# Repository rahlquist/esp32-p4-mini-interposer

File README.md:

# ESP32-P4-Mini Interposer

A small break-out / **interposer** board for the **Spotpear (Waveshare-style) ESP32-P4-Mini development
board** (`ESP32P4-MINI-A`) that adapts its fine-pitch headers up to breadboard-friendly spacing.

## What the board is for

The ESP32-P4-Mini exposes its GPIO on **three dual-row 1.27 mm pin headers** — one on the **left edge (P1)**,
one on the **right edge (P2)**, and one along the **bottom edge (P3)**. 1.27 mm headers are too narrow and
fragile to plug directly into a standard solderless breadboard, which uses 2.54 mm spacing.

This interposer carries **three 1.27 mm female sockets laid out exactly where the Mini's headers are**, so
the Mini plugs down onto it level, and re-routes every one of the 104 pins to **three 2.54 mm single-row
male headers** for easy breadboard / jumper use.

```
       ┌────────────────────────────────────────────┐
       │   P1 (left, vertical)   ──►  J4 (2.54 mm)  │
  Mini │   P2 (right, vertical)  ──►  J5 (2.54 mm)  │
       │   P3 (bottom, horizontal)──► J6 (2.54 mm)  │
       └────────────────────────────────────────────┘
```

The board is a pure passive **1:1 passthrough** — each 1.27 mm input pin is routed straight to the
corresponding 2.54 mm output pin (no level shifting, no logic).

## Key facts

| | |
|---|---|
| Origin board | Spotpear `ESP32P4-MINI-A` — 23.4 × 31.25 mm, ESP32-P4 + ESP32-C6 |
| Input headers | P1 (left, 2×17), P2 (right, 2×17), P3 (bottom, 2×18) — all **1.27 mm** |
| Output headers | J4 (1×34), J5 (1×34), J6 (1×36) — all **2.54 mm** single-row |
| Total nets | 104, one per pin |
| Routing | 2-layer, Freerouting auto-routed; DRC clean (0 unconnected / 0 violations) |
| Silkscreen | Each 2.54 mm output pin labelled with its GPIO / signal name |
| Design | KiCad 10.0.6 (schematic + board) |

## Repository layout

```
.
├── kicad/                 KiCad design source and exports
│   ├── p4-mini-interposer.kicad_sch     schematic
│   ├── p4-mini-interposer.kicad_pcb     routed board
│   ├── p4-mini-interposer.kicad_pro     project
│   ├── p4-mini-interposer.pdf           schematic PDF
│   ├── p4-mini-interposer-routed.pdf    routed board PDF
│   ├── p4-mini-interposer-green.pdf     board render (green solder mask)
│   ├── p4-mini-interposer.ses           Freerouting session
│   └── p4-mini-interposer-bom.csv       bill of materials
├── reference/            Documents/source material the original board is built from
│   ├── esp32p4-mini.pdf   (Spotpear board schematic)
│   ├── esp32-p4-ext.pdf   (extension board schematic)
│   ├── esp32p4-mini.step / esp32p4-mini-2.step   (3D models)
│   └── *.jpg              (board photos)
└── docs/board-preview.png
```

> The files under `reference/` are the source documentation for the **Spotpear ESP32-P4-Mini** board and
> are the property of their respective authors (Spotpear / Waveshare); they are included for reference and
> are not covered by this project's license. The `kicad/` files are this interposer's own design.

## Silkscreen pinout

Each 2.54 mm output header pin is labelled with the function it connects to. Net mapping is a plain 1:1
passthrough, so output header **J4 pin N ↔ mini P1 pin N** (and likewise J5↔P2, J6↔P3):

| Output | Source header | Signals (by pin) |
|---|---|---|
| **J4** | **P1** (left, vertical) | D−, D+, GPIO31…53, 5V, 1V8, 3V3, GND |
| **J5** | **P2** (right, vertical) | GPIO0…30, SDA, SCL, RESET, 5V, 3V3, GND |
| **J6** | **P3** (bottom, horizontal) | I2C0_SDA/SCL, GPIO6/14–19/54, DSI±/CSI±, USBD±, 3V3, GND |

## Status

- Schematic **ERC clean** and board **DRC clean** (104/104 nets routed, 0 violations).
- Header positions on the interposer were derived from the Mini's 23.4 × 31.25 mm form factor and measured
  header spans (P1–P2 outer span 22.2 mm, P1 vertical span 20.7 mm, P3 span 21.9 mm, P3 set 1 mm off the
  bottom edge). **A physical fit-test against the actual board is recommended before fabrication.**

## License

This interposer design (the `kicad/` files and this README) is licensed under the MIT License — see
[LICENSE](LICENSE). Reference/vendor documents in `reference/` remain the property of their authors.

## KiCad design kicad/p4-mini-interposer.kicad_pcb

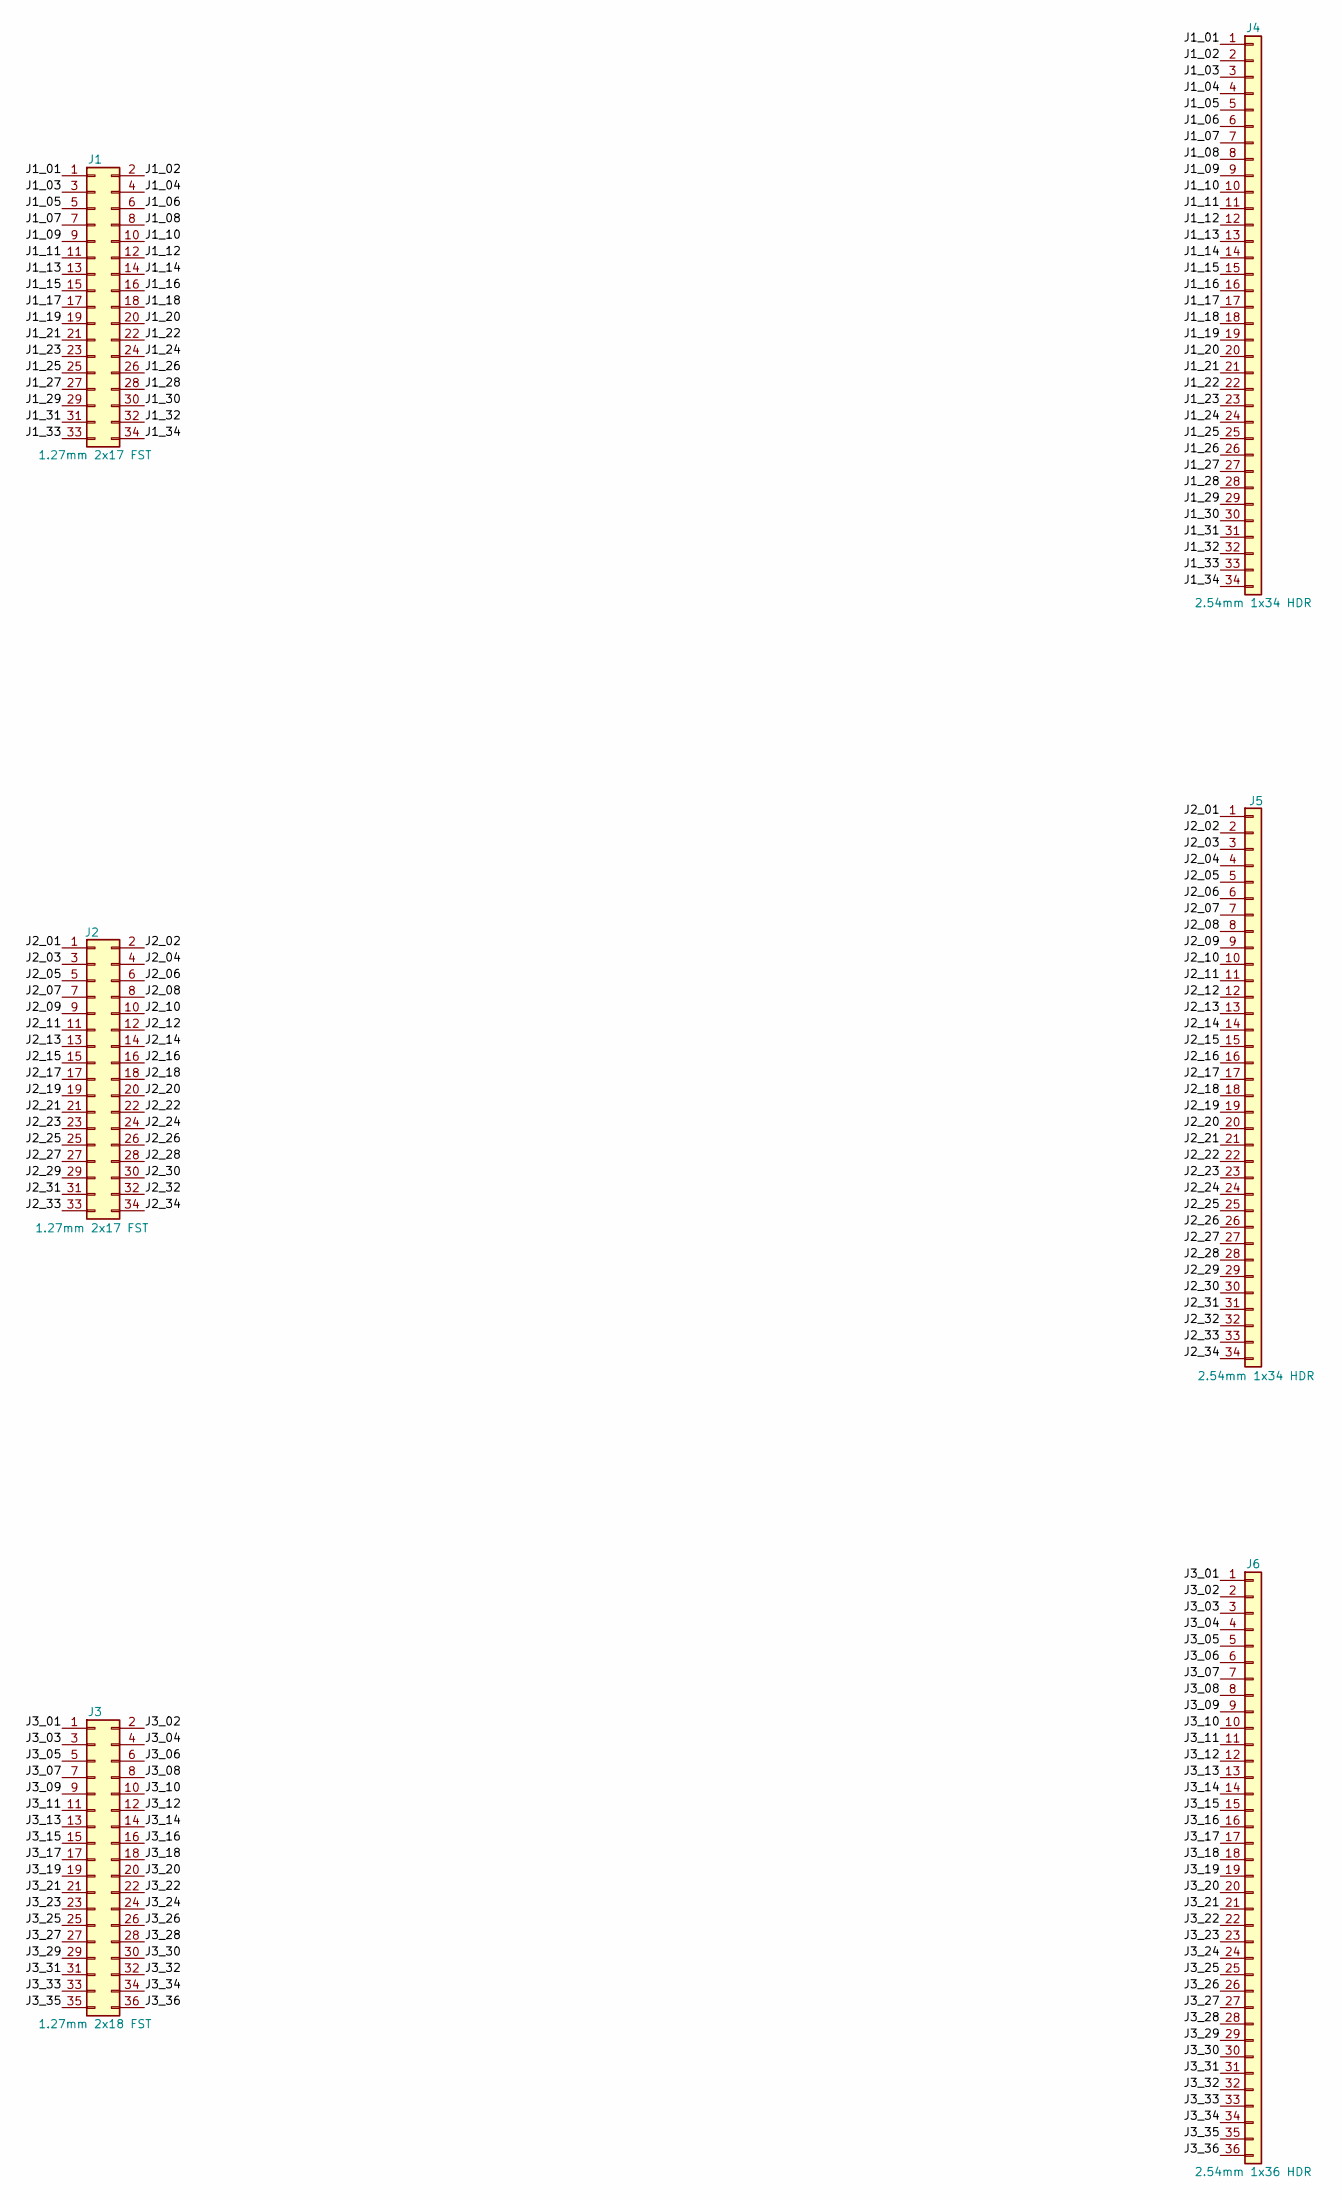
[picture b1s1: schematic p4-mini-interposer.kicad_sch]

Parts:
J1, J2: 1.27mm 2x17 FST; PinHeader_2x17_P1.27mm_Vertical
J3: 1.27mm 2x18 FST; PinHeader_2x18_P1.27mm_Vertical
J4, J5: 2.54mm 1x34 HDR; PinHeader_1x34_P2.54mm_Vertical
J6: 2.54mm 1x36 HDR; PinHeader_1x36_P2.54mm_Vertical

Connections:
/J1_01: J1.1, J4.1
/J1_02: J1.2, J4.2
/J1_03: J1.3, J4.3
/J1_04: J1.4, J4.4
/J1_05: J1.5, J4.5
/J1_06: J1.6, J4.6
/J1_07: J1.7, J4.7
/J1_08: J1.8, J4.8
/J1_09: J1.9, J4.9
/J1_10: J1.10, J4.10
/J1_11: J1.11, J4.11
/J1_12: J1.12, J4.12
/J1_13: J1.13, J4.13
/J1_14: J1.14, J4.14
/J1_15: J1.15, J4.15
/J1_16: J1.16, J4.16
/J1_17: J1.17, J4.17
/J1_18: J1.18, J4.18
/J1_19: J1.19, J4.19
/J1_20: J1.20, J4.20
/J1_21: J1.21, J4.21
/J1_22: J1.22, J4.22
/J1_23: J1.23, J4.23
/J1_24: J1.24, J4.24
/J1_25: J1.25, J4.25
/J1_26: J1.26, J4.26
/J1_27: J1.27, J4.27
/J1_28: J1.28, J4.28
/J1_29: J1.29, J4.29
/J1_30: J1.30, J4.30
/J1_31: J1.31, J4.31
/J1_32: J1.32, J4.32
/J1_33: J1.33, J4.33
/J1_34: J1.34, J4.34
/J2_01: J2.1, J5.1
/J2_02: J2.2, J5.2
/J2_03: J2.3, J5.3
/J2_04: J2.4, J5.4
/J2_05: J2.5, J5.5
/J2_06: J2.6, J5.6
/J2_07: J2.7, J5.7
/J2_08: J2.8, J5.8
/J2_09: J2.9, J5.9
/J2_10: J2.10, J5.10
/J2_11: J2.11, J5.11
/J2_12: J2.12, J5.12
/J2_13: J2.13, J5.13
/J2_14: J2.14, J5.14
/J2_15: J2.15, J5.15
/J2_16: J2.16, J5.16
/J2_17: J2.17, J5.17
/J2_18: J2.18, J5.18
/J2_19: J2.19, J5.19
/J2_20: J2.20, J5.20
/J2_21: J2.21, J5.21
/J2_22: J2.22, J5.22
/J2_23: J2.23, J5.23
/J2_24: J2.24, J5.24
/J2_25: J2.25, J5.25
/J2_26: J2.26, J5.26
/J2_27: J2.27, J5.27
/J2_28: J2.28, J5.28
/J2_29: J2.29, J5.29
/J2_30: J2.30, J5.30
/J2_31: J2.31, J5.31
/J2_32: J2.32, J5.32
/J2_33: J2.33, J5.33
/J2_34: J2.34, J5.34
/J3_01: J3.1, J6.1
/J3_02: J3.2, J6.2
/J3_03: J3.3, J6.3
/J3_04: J3.4, J6.4
/J3_05: J3.5, J6.5
/J3_06: J3.6, J6.6
/J3_07: J3.7, J6.7
/J3_08: J3.8, J6.8
/J3_09: J3.9, J6.9
/J3_10: J3.10, J6.10
/J3_11: J3.11, J6.11
/J3_12: J3.12, J6.12
/J3_13: J3.13, J6.13
/J3_14: J3.14, J6.14
/J3_15: J3.15, J6.15
/J3_16: J3.16, J6.16
/J3_17: J3.17, J6.17
/J3_18: J3.18, J6.18
/J3_19: J3.19, J6.19
/J3_20: J3.20, J6.20
/J3_21: J3.21, J6.21
/J3_22: J3.22, J6.22
/J3_23: J3.23, J6.23
/J3_24: J3.24, J6.24
/J3_25: J3.25, J6.25
/J3_26: J3.26, J6.26
/J3_27: J3.27, J6.27
/J3_28: J3.28, J6.28
/J3_29: J3.29, J6.29
/J3_30: J3.30, J6.30
/J3_31: J3.31, J6.31
/J3_32: J3.32, J6.32
/J3_33: J3.33, J6.33
/J3_34: J3.34, J6.34
/J3_35: J3.35, J6.35
/J3_36: J3.36, J6.36

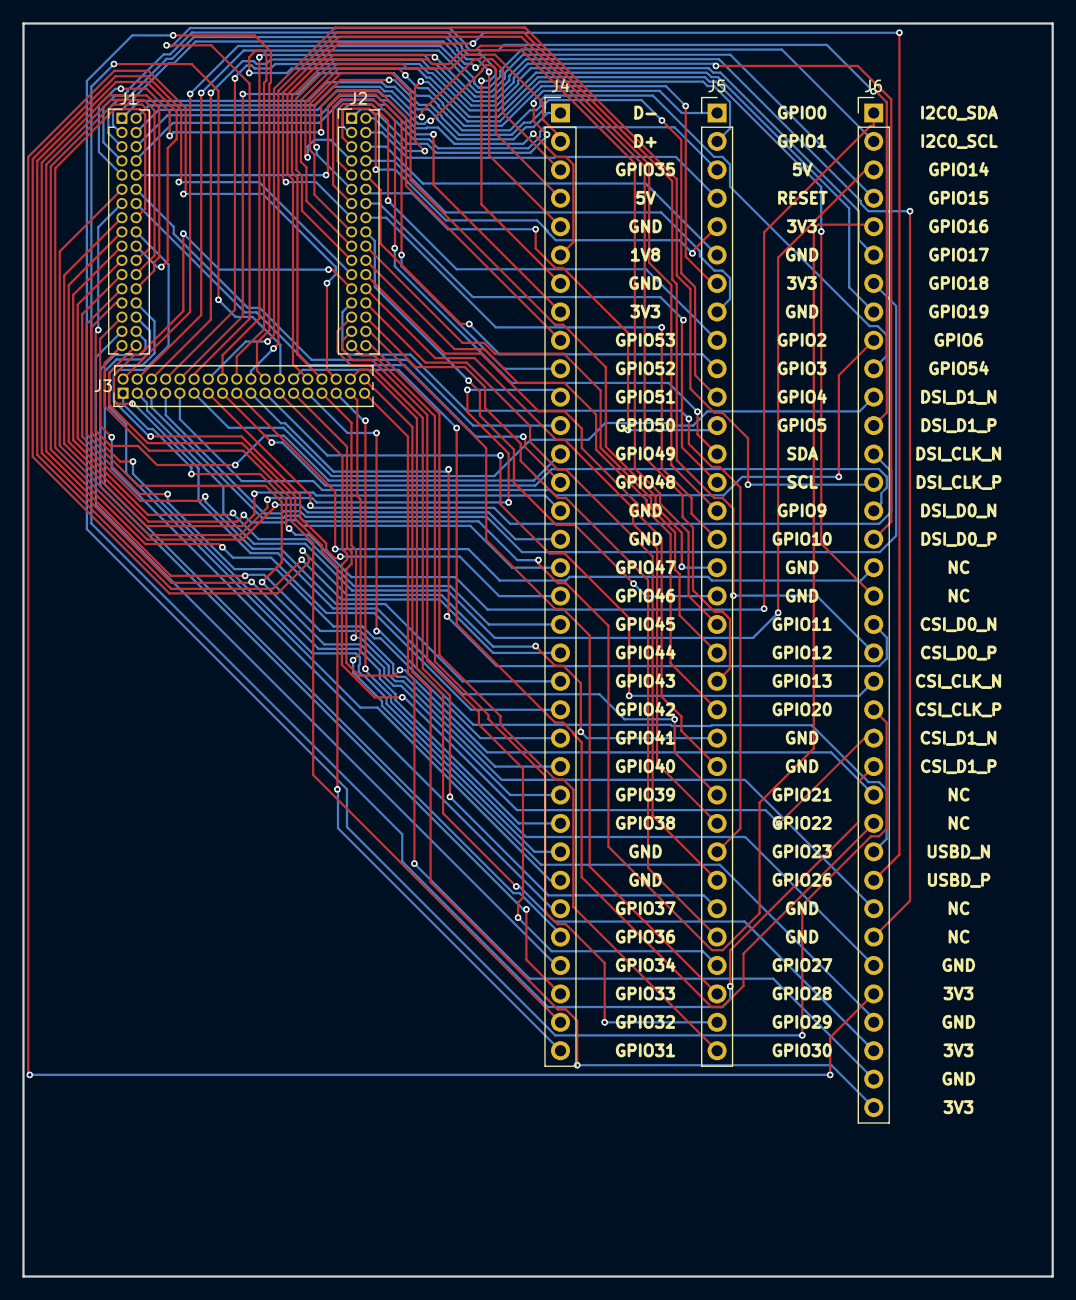
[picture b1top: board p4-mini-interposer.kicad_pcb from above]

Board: 2 copper layers, 92.0 x 112.0 mm, 6 parts (0 on the bottom side), 104 nets.

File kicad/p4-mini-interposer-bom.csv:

"Refs","Value","Footprint","Qty","DNP"
"J1","1.27mm 2x17 FST","Connector_PinHeader_1.27mm:PinHeader_2x17_P1.27mm_Vertical","1",""
"J2","1.27mm 2x17 FST","Connector_PinHeader_1.27mm:PinHeader_2x17_P1.27mm_Vertical","1",""
"J3","1.27mm 2x18 FST","Connector_PinHeader_1.27mm:PinHeader_2x18_P1.27mm_Vertical","1",""
"J4","2.54mm 1x34 HDR","Connector_PinHeader_2.54mm:PinHeader_1x34_P2.54mm_Vertical","1",""
"J5","2.54mm 1x34 HDR","Connector_PinHeader_2.54mm:PinHeader_1x34_P2.54mm_Vertical","1",""
"J6","2.54mm 1x36 HDR","Connector_PinHeader_2.54mm:PinHeader_1x36_P2.54mm_Vertical","1",""
